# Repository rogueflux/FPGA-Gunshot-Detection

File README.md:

# Gunshot Detection and Localization System

## Overview
A lightweight, real-time gunshot detection and localization system designed for edge deployment on FPGA platforms. The system uses a six-microphone hexagonal array and an attention-augmented MobileNet1D neural network to detect gunshots with high recall, followed by MUSIC-based localization for directional estimation.

**Key Capabilities:**
- Real-time gunshot detection with 98.22% recall
- 2D source localization using MUSIC algorithm
- Ultra-low latency (6.03 ms end-to-end)
- Edge-optimized for FPGA deployment

## Project Structure

```
gunshot_detection_fpga/
├── notebooks/                    # Jupyter notebooks for R&D
│   ├── Bi_Audioprocessor_and_extractor.ipynb
│   ├── Gunshot_NewAttentionModel.ipynb
│   └── Source_Separation_MUSIC_algorithm.ipynb
├── python/                       # Production Python code
├── hardware/                     # FPGA implementation
├── firmware/                     # Embedded software
├── models/                       # Trained models and conversion
├── scripts/                      # Build and deployment scripts
├── docs/                         # Documentation
└── tests/                        # Test suites
```

## Quick Start

### Prerequisites
- Python 3.8+
- Xilinx Vivado 2022.1
- Xilinx Vitis HLS 2022.1
- PyTorch 1.12+

### Installation
```bash
# Clone repository
git clone <repository-url>
cd gunshot_detection_fpga

# Install Python dependencies
pip install -r requirements.txt

# Setup environment variables
source scripts/setup_environment.sh
```

### Training the Model
```bash
# Train the attention-augmented MobileNet1D
python python/gunshot_model/train.py --config configs/train_config.yaml

# Convert to HLS-compatible format
python models/convert_pytorch_to_hls.py --model models/gunshot_model_weights.pth
```

### FPGA Deployment
```bash
# Complete build (FPGA bitstream + firmware)
./scripts/complete_build.sh

# Program FPGA
./scripts/program_fpga.sh --device /dev/ttyUSB0

# Run system test
./scripts/test_system.py
```

## System Performance

### Detection Metrics
| Metric | Value |
|--------|-------|
| Accuracy | 89.89% |
| **Recall (Gunshot)** | **98.22%** |
| Precision | 72.22% |
| F1-Score | 0.8324 |
| ROC AUC | 0.9826 |

### Hardware Performance
| Platform | Latency | Power | Throughput |
|----------|---------|-------|------------|
| **FPGA (Spartan-7)** | **6.03 ms** | **305 mW** | **165 fps** |
| Raspberry Pi 4 | 45 ms | 4.5 W | 22 fps |
| Cloud (AWS) | 120 ms | N/A | 80 fps |

## Hardware Implementation

### Target Platform
- **FPGA**: Xilinx Spartan-7 XC7S50T
- **Microphones**: 6× INMP441 MEMS array (hexagonal)
- **Interfaces**: I2S audio, UART, GPIO alerts

### Resource Utilization
| Resource | Used | Available | Utilization |
|----------|------|-----------|-------------|
| LUTs | 28,450 | 52,160 | 54.5% |
| BRAM | 65 | 145 | 44.8% |
| DSP Slices | 120 | 200 | 60.0% |

## Model Architecture

### Attention-Augmented MobileNet1D
- **Parameters**: 18,000 (~80 KB)
- **Input**: 2052-dimensional spectral features
- **Architecture**:
  1. Initial 1D convolution (1→48 channels)
  2. 3× depthwise separable blocks
  3. Squeeze-and-Excitation attention
  4. 3-layer classifier (128→64→32→2)

### MUSIC Localization
- **Algorithm**: Multiple Signal Classification
- **Output**: 2D source position (x, y)
- **Confidence**: Peak sharpness-based certainty

## Development Workflow

### 1. Research & Experimentation
```python
# Explore in Jupyter notebooks
jupyter notebook notebooks/Gunshot_NewAttentionModel.ipynb
```

### 2. Model Development
```bash
# Train and validate model
python python/gunshot_model/train.py

# Test preprocessing pipeline
python python/preprocessing/audio_processor.py --audio sample.wav
```

### 3. FPGA Implementation
```bash
# Convert model to HLS
python models/convert_pytorch_to_hls.py

# Build FPGA project
cd hardware/vivado
vivado -source vivado_project.tcl

# Synthesize HLS IP
cd ../vitis_hls
vitis_hls -f hls_script.tcl
```

### 4. System Integration
```bash
# Build complete system
./scripts/complete_build.sh

# Deploy and test
./scripts/test_system.py --mode hardware
```

## Key Files

### Notebooks
- `Bi_Audioprocessor_and_extractor.ipynb`: Audio preprocessing and feature extraction
- `Gunshot_NewAttentionModel.ipynb`: Attention model development and training
- `Source_Separation_MUSIC_algorithm.ipynb`: Localization algorithm implementation

### Python Modules
- `python/gunshot_model/attention_model.py`: Neural network architecture
- `python/preprocessing/feature_extractor.py`: STFT-based feature extraction
- `python/preprocessing/music_algorithm.py`: MUSIC localization implementation

### FPGA Sources
- `hardware/vitis_hls/gunshot_detector_hls_complete.cpp`: HLS-optimized model
- `hardware/vivado/spartan_edge_accel_gunshot.xdc`: Timing constraints
- `firmware/src/music_localization.c`: Embedded MUSIC implementation

## Testing

### Unit Tests
```bash
# Run Python unit tests
python -m pytest tests/unit_tests/

# Run hardware simulation tests
cd tests/hardware_tests/
./run_simulation.sh
```

### System Validation
```bash
# Full system test with recorded audio
./scripts/test_system.py --audio data/audio_samples/test_gunshot.wav

# Hardware-in-the-loop test
./scripts/test_system.py --mode hardware --duration 60
```

## Applications

### Public Safety
- Real-time urban gunshot surveillance
- Rapid police response coordination
- Forensic evidence collection

### Smart Cities
- Distributed acoustic sensor networks
- Edge-deployed IoT monitoring
- Critical infrastructure protection

### Conservation
- Anti-poaching in protected areas
- Remote wildlife monitoring
- Low-power field deployment

## Performance Optimization

### Model Compression
```bash
# 8-bit quantization (4× memory reduction)
python models/quantize_model.py --model gunshot_model_weights.pth --bits 8

# Pruning (30% sparsity)
python models/prune_model.py --model gunshot_model_weights.pth --sparsity 0.3
```

### FPGA Optimization
```cpp
// HLS pragmas for optimization
#pragma HLS PIPELINE II=1
#pragma HLS ARRAY_PARTITION variable=input cyclic factor=16
#pragma HLS UNROLL factor=8
```

## Contributing

1. **Fork the repository**
2. **Create a feature branch**
3. **Add tests for new functionality**
4. **Submit a pull request**

### Development Guidelines
- Maintain 98%+ recall for gunshot class
- Keep model under 25,000 parameters
- Ensure <10 ms latency on target hardware
- Document all public APIs

## License

This project is licensed under the Apache 2.0 License - see the [LICENSE](LICENSE) file for details.

## Contact

**My Contact**  
Email: priyanshu.sil.201529@gmail.com  

## Acknowledgments

- Based on research from Kabir et al. (2022) and Morehead et al. (2019)
- Implemented on Digilent Spartan Edge Accelerator platform
- Tested with custom-collected urban audio dataset

---

**Safety Note:** This system is designed for public safety applications. Always verify detections through secondary means before initiating emergency responses. False positive rate: 12.98% - implement appropriate alert verification protocols.

**Last Updated:** December 2025  
**Version:** 1.0.0  
**Compatibility:** Python 3.8+, Vivado 2022.1+, Spartan-7 FPGA

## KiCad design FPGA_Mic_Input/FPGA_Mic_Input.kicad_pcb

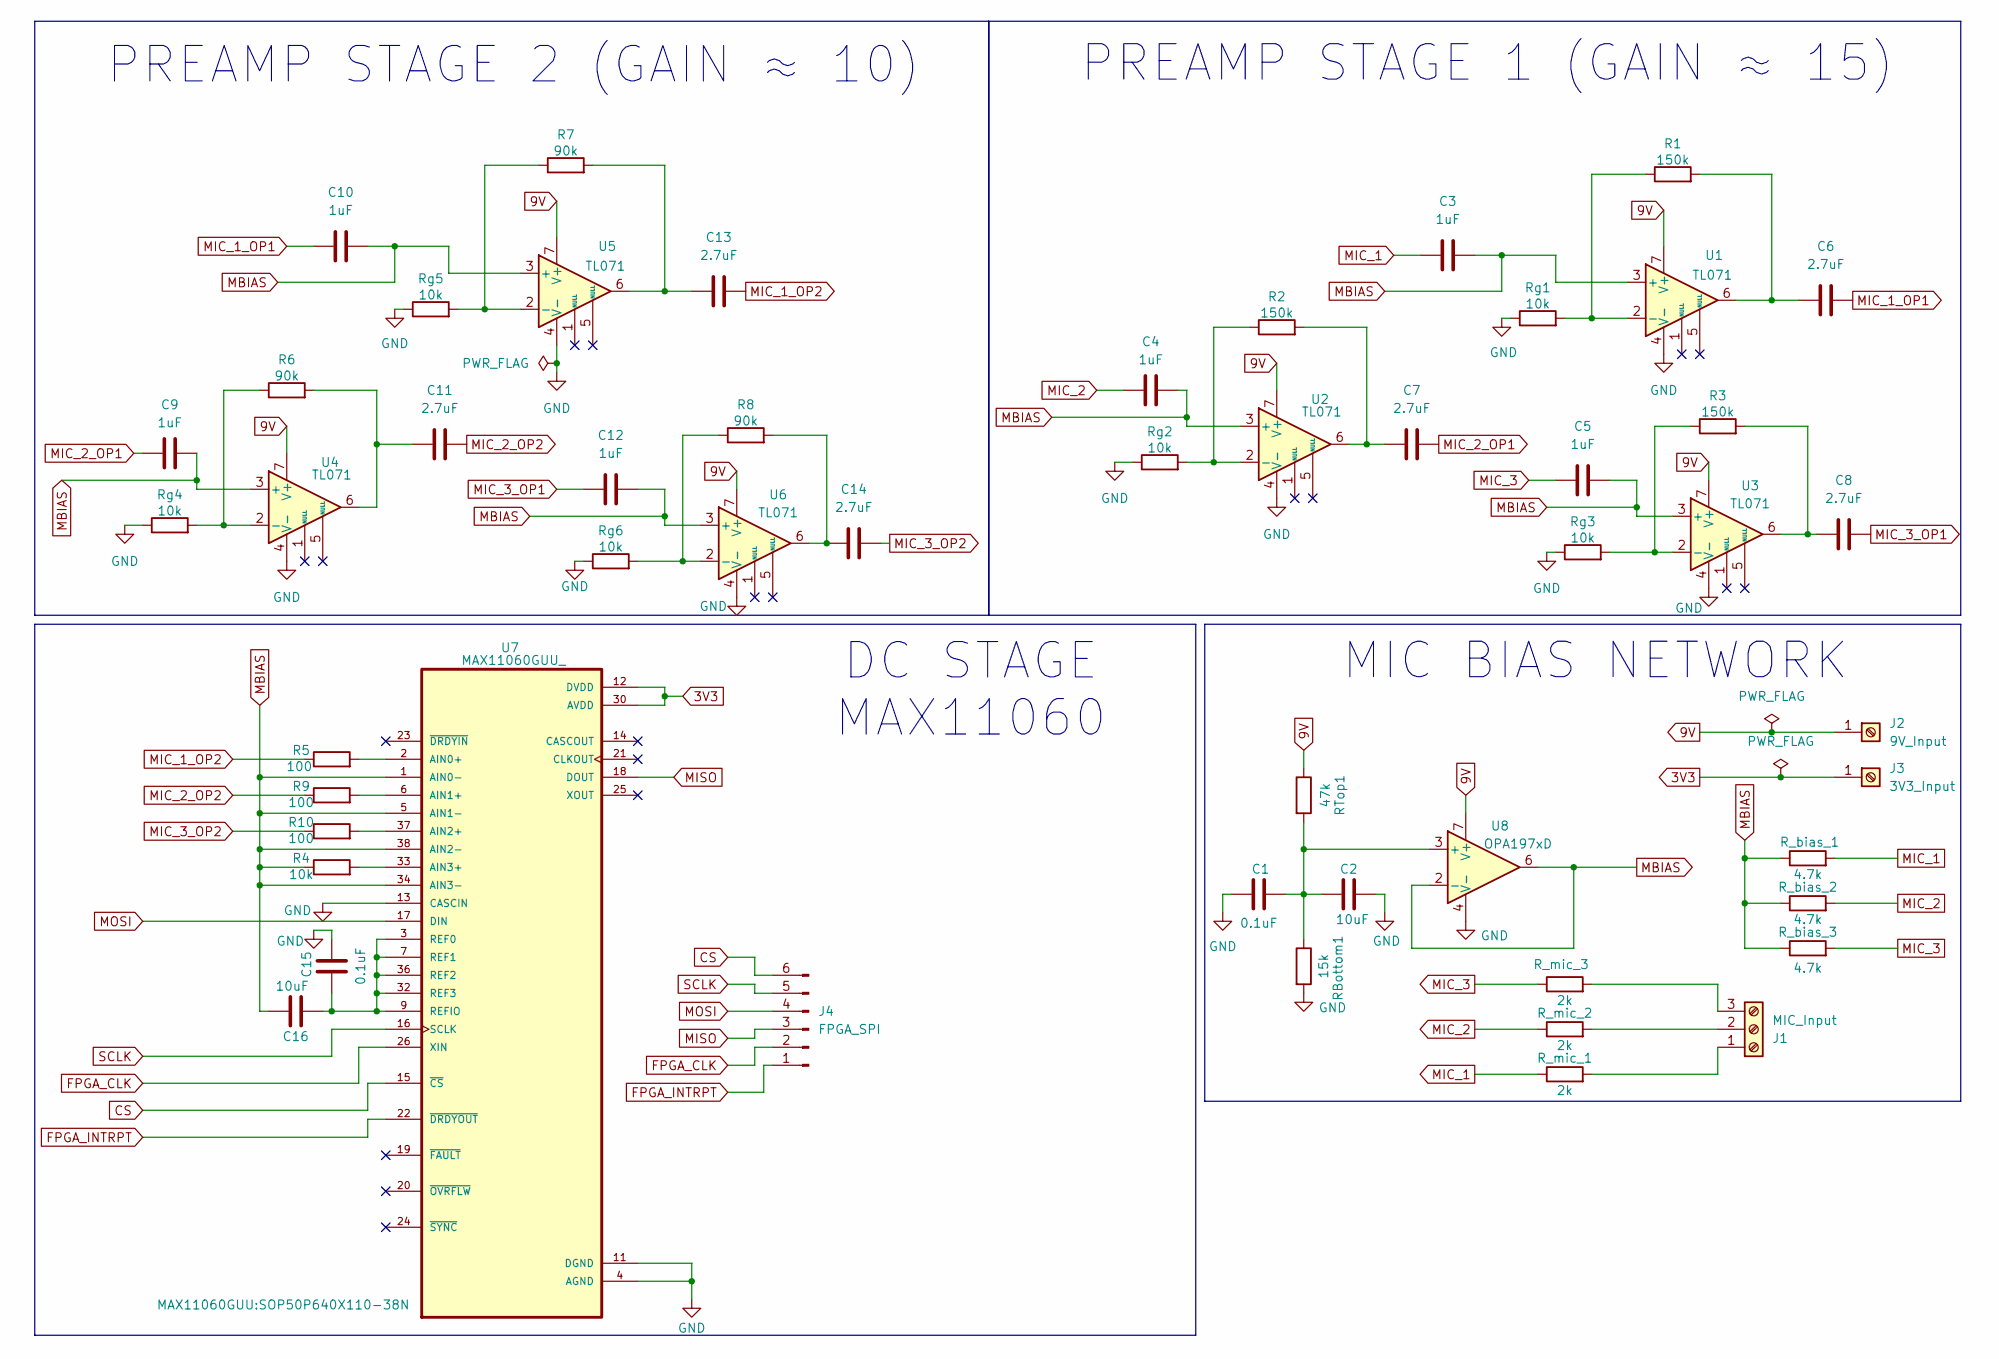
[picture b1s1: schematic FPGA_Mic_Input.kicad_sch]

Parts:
C1, C15: 0.1uF; C_Disc_D3.0mm_W2.0mm_P2.50mm
C2, C16: 10uF; C_Disc_D3.0mm_W2.0mm_P2.50mm
C3, C4, C5, C9, C10, C12: 1uF; C_Disc_D3.0mm_W2.0mm_P2.50mm
C6, C7, C8, C11, C13, C14: 2.7uF; C_Disc_D3.0mm_W2.0mm_P2.50mm
J1: MIC_Input; TerminalBlock_Altech_AK300-3_P5.00mm
J2: 9V_Input; TerminalBlock_MetzConnect_360271_1x01_Horizontal_ScrewM3.0_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
J3: 3V3_Input; TerminalBlock_MetzConnect_360271_1x01_Horizontal_ScrewM3.0_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
J4: FPGA_SPI; JST_EH_B6B-EH-A_1x06_P2.50mm_Vertical
R1, R2, R3: 150k; R_Axial_DIN0204_L3.6mm_D1.6mm_P7.62mm_Horizontal
R4: 10k; R_Axial_DIN0204_L3.6mm_D1.6mm_P7.62mm_Horizontal
R5, R9, R10: 100; R_Axial_DIN0204_L3.6mm_D1.6mm_P7.62mm_Horizontal
R6, R7, R8: 90k; R_Axial_DIN0204_L3.6mm_D1.6mm_P7.62mm_Horizontal
RBottom1: 15k; R_Axial_DIN0204_L3.6mm_D1.6mm_P7.62mm_Horizontal
RTop1: 47k; R_Axial_DIN0204_L3.6mm_D1.6mm_P7.62mm_Horizontal
R_bias_1, R_bias_2, R_bias_3: 4.7k; R_Axial_DIN0204_L3.6mm_D1.6mm_P7.62mm_Horizontal
R_mic_1, R_mic_2, R_mic_3: 2k; R_Axial_DIN0204_L3.6mm_D1.6mm_P7.62mm_Horizontal
Rg1, Rg2, Rg3, Rg4, Rg5, Rg6: 10k; R_Axial_DIN0204_L3.6mm_D1.6mm_P7.62mm_Horizontal
U1, U2, U3, U4, U5, U6: TL071; DIP-8-16_W7.62mm
U7: MAX11060GUU_; SOP50P640X110-38N; DigiKey_Part_Number MAX11060GUU+-ND
U8: OPA197xD; SOIC-8_3.9x4.9mm_P1.27mm

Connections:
3V3: J3.1, U7.12 (DVDD), U7.27 (DVDD), U7.30 (AVDD)
9V: J2.1, RTop1.1, U1.7 (V+), U2.7 (V+), U3.7 (V+), U4.7 (V+), U5.7 (V+), U6.7 (V+), U8.7 (V+)
CS: J4.6, U7.15 (~CS)
FPGA_CLK: J4.2, U7.26 (XIN)
FPGA_INTRPT: J4.1, U7.22 (~DRDYOUT)
GND: C1.1, C2.2, C15.2, RBottom1.2, Rg1.1, Rg2.1, Rg3.1, Rg4.1, Rg5.1, Rg6.1, U1.4 (V-), U2.4 (V-), U3.4 (V-), U4.4 (V-), U5.4 (V-), U6.4 (V-), U7.4 (AGND), U7.8 (AGND), U7.10 (AGND), U7.11 (DGND), U7.13 (CASCIN), U7.28 (DGND), U7.29 (AGND), U7.31 (AGND), U7.35 (AGND), U8.4 (V-)
MBIAS: C3.2, C4.2, C5.2, C9.2, C10.2, C12.2, C16.2, R4.1, R_bias_1.1, R_bias_2.1, R_bias_3.1, U1.3 (+), U2.3 (+), U3.3 (+), U4.3 (+), U5.3 (+), U6.3 (+), U7.1 (AIN0-), U7.5 (AIN1-), U7.34 (AIN3-), U7.38 (AIN2-), U8.2 (-), U8.6
MIC_1: C3.1, R_bias_1.2, R_mic_1.1
MIC_1_OP1: C6.2, C10.1
MIC_1_OP2: C13.2, R5.1
MIC_2: C4.1, R_bias_2.2, R_mic_2.1
MIC_2_OP1: C7.2, C9.1
MIC_2_OP2: C11.2, R9.1
MIC_3: C5.1, R_bias_3.2, R_mic_3.1
MIC_3_OP1: C8.2, C12.1
MIC_3_OP2: C14.2, R10.1
MISO: J4.3, U7.18 (DOUT)
MOSI: J4.4, U7.17 (DIN)
unnamed: C6.1, R1.2, U1.6
unnamed: C7.1, R2.2, U2.6
unnamed: C8.1, R3.2, U3.6
unnamed: C11.1, R6.2, U4.6
unnamed: C13.1, R7.2, U5.6
unnamed: C14.1, R8.2, U6.6
unnamed: J1.1, R_mic_1.2
unnamed: J1.2, R_mic_2.2
unnamed: J1.3, R_mic_3.2
unnamed: R1.1, Rg1.2, U1.2 (-)
unnamed: R2.1, Rg2.2, U2.2 (-)
unnamed: R3.1, Rg3.2, U3.2 (-)
unnamed: R6.1, Rg4.2, U4.2 (-)
unnamed: R7.1, Rg5.2, U5.2 (-)
unnamed: R8.1, Rg6.2, U6.2 (-)
unnamed: R5.2, U7.2 (AIN0+)
unnamed: R9.2, U7.6 (AIN1+)
unnamed: R10.2, U7.37 (AIN2+)
unnamed: R4.2, U7.33 (AIN3+)
unnamed: C15.1, C16.1, U7.3 (REF0), U7.7 (REF1), U7.9 (REFIO), U7.32 (REF3), U7.36 (REF2)
unnamed: C1.2, C2.1, RBottom1.1, RTop1.2, U8.3 (+)
SCLK: J4.5, U7.16 (SCLK)

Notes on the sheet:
PREAMP STAGE 2 (GAIN ≈ 10)
DC STAGE MAX11060
MIC BIAS NETWORK
PREAMP STAGE 1 (GAIN ≈ 15)

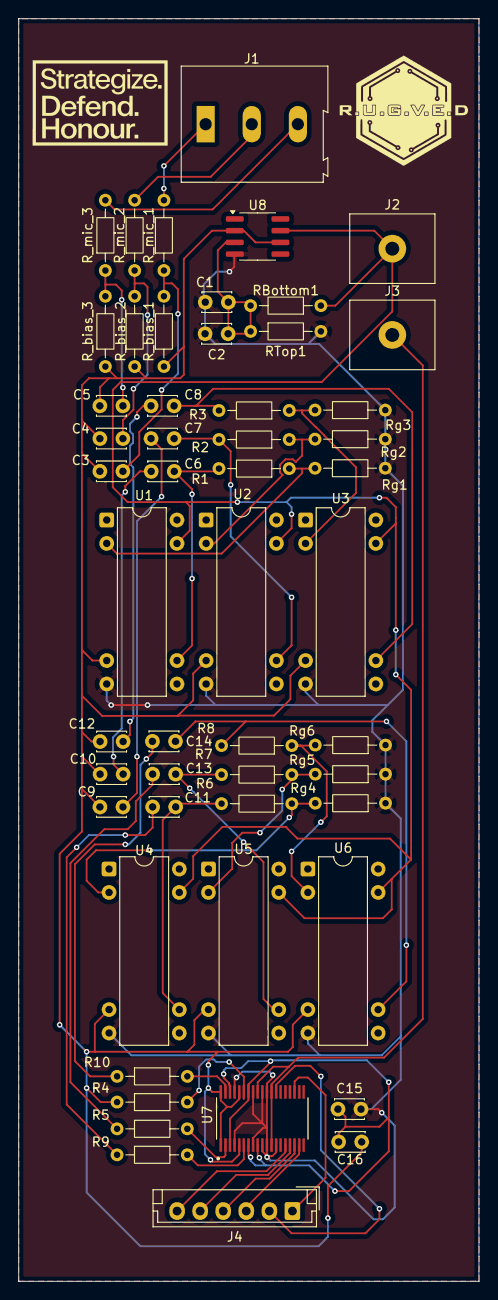
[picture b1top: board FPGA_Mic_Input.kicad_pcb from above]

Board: 2 copper layers, 49.9 x 136.9 mm, 52 parts (0 on the bottom side), 40 nets.

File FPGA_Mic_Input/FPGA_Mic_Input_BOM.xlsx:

Reference | Qty | Value | Manufacturer | MPN | DNP | Exclude from BOM | Exclude from Board | Footprint | Datasheet
C1,C15 | 2 | 0.1uF | Generic | Generic 0.1uF Ceramic |  |  |  | Capacitor_THT:C_Disc_D3.0mm_W2.0mm_P2.50mm | ~
C2,C16 | 2 | 10uF | Generic | Generic 10uF Ceramic |  |  |  | Capacitor_THT:C_Disc_D3.0mm_W2.0mm_P2.50mm | ~
C3,C4,C5,C9,C10,C12 | 6 | 1uF | Generic | Generic 1uF Ceramic |  |  |  | Capacitor_THT:C_Disc_D3.0mm_W2.0mm_P2.50mm | ~
C6,C7,C8,C11,C13,C14 | 6 | 2.7uF | Generic | Generic 2.7uF Ceramic |  |  |  | Capacitor_THT:C_Disc_D3.0mm_W2.0mm_P2.50mm | ~
J1 | 1 | MIC_Input | Altech | AK300-3 |  |  |  | TerminalBlock:TerminalBlock_Altech_AK300-3_P5.00mm | ~
J2 | 1 | 9V_Input | Metz Connect | 360271 |  |  |  | TerminalBlock_MetzConnect:TerminalBlock_MetzConnect_360271_1x01_Horizontal_Scre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 | ~
J3 | 1 | 3V3_Input | Metz Connect | 360271 |  |  |  | TerminalBlock_MetzConnect:TerminalBlock_MetzConnect_360271_1x01_Horizontal_Scre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 | ~
J4 | 1 | FPGA_SPI | JST | B6B-EH-A |  |  |  | Connector_JST:JST_EH_B6B-EH-A_1x06_P2.50mm_Vertical | ~
R1,R2,R3 | 3 | 150k | Generic | Generic 150k 1/4W |  |  |  | Resistor_THT:R_Axial_DIN0204_L3.6mm_D1.6mm_P7.62mm_Horizontal | ~
R4,Rg1,Rg2,Rg3,Rg4,Rg5,Rg6 | 7 | 10k | Generic | Generic 10k 1/4W |  |  |  | Resistor_THT:R_Axial_DIN0204_L3.6mm_D1.6mm_P7.62mm_Horizontal | ~
R5,R9,R10 | 3 | 100 | Generic | Generic 100Ω 1/4W |  |  |  | Resistor_THT:R_Axial_DIN0204_L3.6mm_D1.6mm_P7.62mm_Horizontal | ~
R6,R7,R8 | 3 | 90k | Generic | Generic 90k 1/4W |  |  |  | Resistor_THT:R_Axial_DIN0204_L3.6mm_D1.6mm_P7.62mm_Horizontal | ~
RBottom1 | 1 | 15k | Generic | Generic 15k 1/4W |  |  |  | Resistor_THT:R_Axial_DIN0204_L3.6mm_D1.6mm_P7.62mm_Horizontal | ~
RTop1 | 1 | 47k | Generic | Generic 47k 1/4W |  |  |  | Resistor_THT:R_Axial_DIN0204_L3.6mm_D1.6mm_P7.62mm_Horizontal | ~
R_bias_1,R_bias_2,R_bias_3 | 3 | 4.7k | Generic | Generic 4.7k 1/4W |  |  |  | Resistor_THT:R_Axial_DIN0204_L3.6mm_D1.6mm_P7.62mm_Horizontal | ~
R_mic_1,R_mic_2,R_mic_3 | 3 | 2k | Generic | Generic 2k 1/4W |  |  |  | Resistor_THT:R_Axial_DIN0204_L3.6mm_D1.6mm_P7.62mm_Horizontal | ~
U1,U2,U3,U4,U5,U6 | 6 | TL071 | Texas Instruments | TL071IP |  |  |  | Package_DIP:DIP-8-16_W7.62mm | http://www.ti.com/lit/ds/symlink/tl071.pdf
U7 | 1 | MAX11060GUU_ | Analog Devices | MAX11060GUU+ |  |  |  | MAX11060GUU:SOP50P640X110-38N | https://www.analog.com/media/en/technical-documentation/data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
U8 | 1 | OPA197xD | Texas Instruments | OPA197ID |  |  |  | Package_SO:SOIC-8_3.9x4.9mm_P1.27mm | http://www.ti.com/lit/ds/symlink/opa197.pdf

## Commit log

2026-01-30 Create LICENSE
